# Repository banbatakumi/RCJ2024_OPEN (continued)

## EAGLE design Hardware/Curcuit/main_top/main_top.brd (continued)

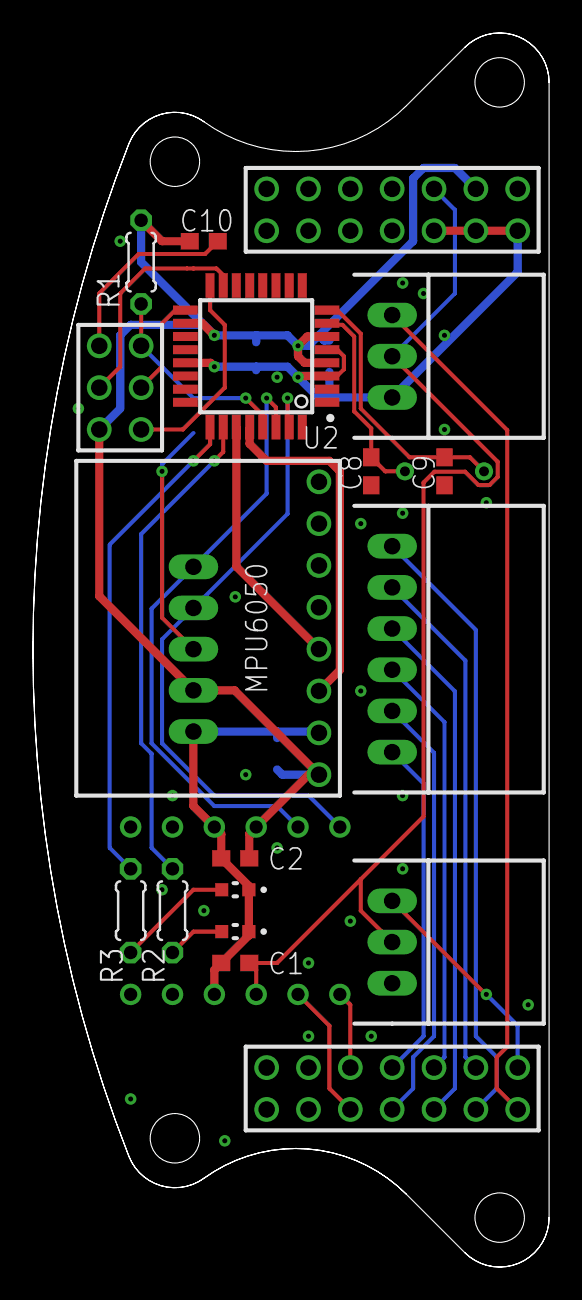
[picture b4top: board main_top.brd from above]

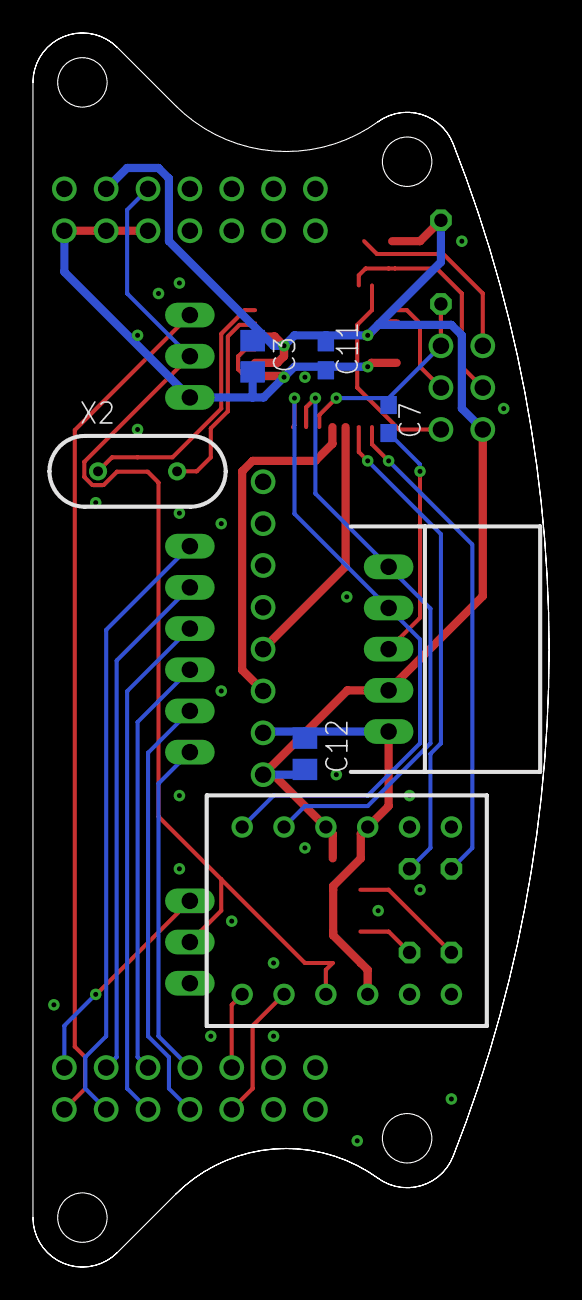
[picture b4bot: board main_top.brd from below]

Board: 2 copper layers, 31.3 x 74.9 mm, 25 parts (7 on the bottom side), 28 nets.

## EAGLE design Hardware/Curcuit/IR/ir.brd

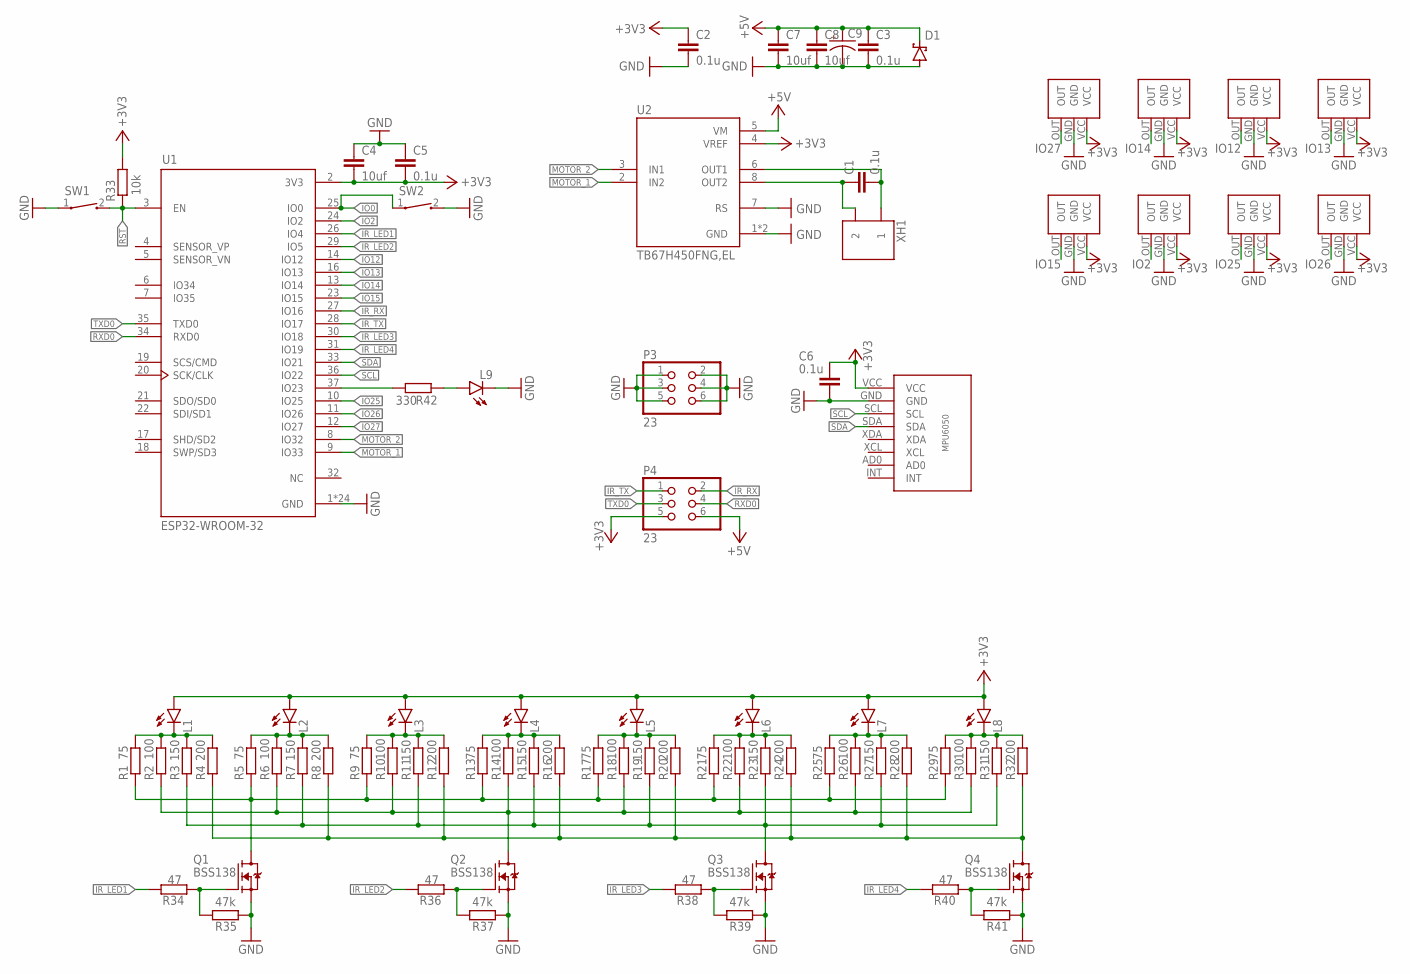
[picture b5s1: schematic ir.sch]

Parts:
C1, C2, C3, C5, C6: 0.1u; C0603
C4, C7, C8: 10uf; C0805
C9: MH5
D1: SS2040FL; SOD123FL
IR1, IR2, IR3, IR4, IR5, IR6, IR7, IR8: TSSP4038
L1, L2, L3, L4, L5, L6, L7, L8: LED
L9: SML-E12P8WT86; LED_SML-LXFM0603SIC-TR
P3, P4: 23; 2*3
Q1, Q2, Q3, Q4: BSS138; SOT95P240X111-3N
R1, R5, R9, R13, R17, R21, R25, R29: 75; R0603
R2, R6, R10, R14, R18, R22, R26, R30: 100; R0603
R3, R7, R11, R15, R19, R23, R27, R31: 150; R0603
R4, R8, R12, R16, R20, R24, R28, R32: 200; R0603
R33: 10k; R0603
R34, R36, R38, R40: 47; R0603
R35, R37, R39, R41: 47k; R0603
R42: 330; R0603
SW1, SW2: TATE
U1: ESP32-WROOM-32; MODULE_ESP32-WROOM-32
U2: TB67H450FNG,EL; SOIC127P599X175-9N
U$1: MPU6050
XH1: S2B

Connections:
+3V3: C2.1, C4.2, C5.2, C6.1, IR1.VCC, IR2.VCC, IR3.VCC, IR4.VCC, IR5.VCC, IR6.VCC, IR7.VCC, IR8.VCC, L1.+, L2.+, L3.+, L4.+, L5.+, L6.+, L7.+, L8.+, P4.5, R33.2, U1.2 (3V3), U2.4 (VREF), U$1.VCC
+5V: C3.1, C7.1, C8.1, C9.+, D1.C, P4.6, U2.5 (VM)
GND: C2.2, C3.2, C4.1, C5.1, C6.2, C7.2, C8.2, C9.-, D1.A, IR1.GND, IR2.GND, IR3.GND, IR4.GND, IR5.GND, IR6.GND, IR7.GND, IR8.GND, L9.C, P3.1, P3.2, P3.3, P3.4, P3.5, P3.6, Q1.2 (S), Q2.2 (S), Q3.2 (S), Q4.2 (S), R35.2, R37.2, R39.2, R41.2, SW1.1, SW2.2, U1.1 (GND), U1.15 (GND), U1.38 (GND), U1.39_1 (GND), U1.39_2 (GND), U1.39_3 (GND), U1.39_4 (GND), U1.39_5 (GND), U1.39_6 (GND), U1.39_7 (GND), U1.39_8 (GND), U1.39_9 (GND), U1.39_10 (GND), U1.39_11 (GND), U1.39_12 (GND), U1.39_13 (GND), U1.39_14 (GND), U1.39_15 (GND), U1.39_16 (GND), U1.39_17 (GND), U1.39_18 (GND), U1.39_19 (GND), U1.39_20 (GND), U1.39_21 (GND), U2.1 (GND), U2.7 (RS), U2.9 (GND), U$1.GND
IO0: SW2.1, U1.25 (IO0)
IO2: IR6.OUT, U1.24 (IO2)
IO12: IR3.OUT, U1.14 (IO12)
IO13: IR4.OUT, U1.16 (IO13)
IO14: IR2.OUT, U1.13 (IO14)
IO15: IR5.OUT, U1.23 (IO15)
IO25: IR7.OUT, U1.10 (IO25)
IO26: IR8.OUT, U1.11 (IO26)
IO27: IR1.OUT, U1.12 (IO27)
IR_LED1: R34.2, U1.26 (IO4)
IR_LED2: R36.2, U1.29 (IO5)
IR_LED3: R38.2, U1.30 (IO18)
IR_LED4: R40.2, U1.31 (IO19)
IR_RX: P4.2, U1.27 (IO16)
IR_TX: P4.1, U1.28 (IO17)
MOTOR_1: U1.9 (IO33), U2.2 (IN2)
MOTOR_2: U1.8 (IO32), U2.3 (IN1)
unnamed: C1.2, U2.6 (OUT1), XH1.1
unnamed: C1.1, U2.8 (OUT2), XH1.2
unnamed: L1.-, R1.2, R2.2, R3.2, R4.2
unnamed: L2.-, R5.2, R6.2, R7.2, R8.2
unnamed: L3.-, R9.2, R10.2, R11.2, R12.2
unnamed: L4.-, R13.2, R14.2, R15.2, R16.2
unnamed: L5.-, R17.2, R18.2, R19.2, R20.2
unnamed: L6.-, R21.2, R22.2, R23.2, R24.2
unnamed: L7.-, R25.2, R26.2, R27.2, R28.2
unnamed: L8.-, R29.2, R30.2, R31.2, R32.2
unnamed: Q1.3 (D), R1.1, R5.1, R9.1, R13.1, R17.1, R21.1, R25.1, R29.1
unnamed: Q2.3 (D), R2.1, R6.1, R10.1, R14.1, R18.1, R22.1, R26.1, R30.1
unnamed: Q3.3 (D), R3.1, R7.1, R11.1, R15.1, R19.1, R23.1, R27.1, R31.1
unnamed: Q4.3 (D), R4.1, R8.1, R12.1, R16.1, R20.1, R24.1, R28.1, R32.1
unnamed: Q1.1 (G), R34.1, R35.1
unnamed: Q2.1 (G), R36.1, R37.1
unnamed: Q3.1 (G), R38.1, R39.1
unnamed: Q4.1 (G), R40.1, R41.1
unnamed: L9.A, R42.1
unnamed: R42.2, U1.37 (IO23)
RST: R33.1, SW1.2, U1.3 (EN)
RXD0: P4.4, U1.34 (RXD0)
SCL: U1.36 (IO22), U$1.SCL
SDA: U1.33 (IO21), U$1.SDA
TXD0: P4.3, U1.35 (TXD0)

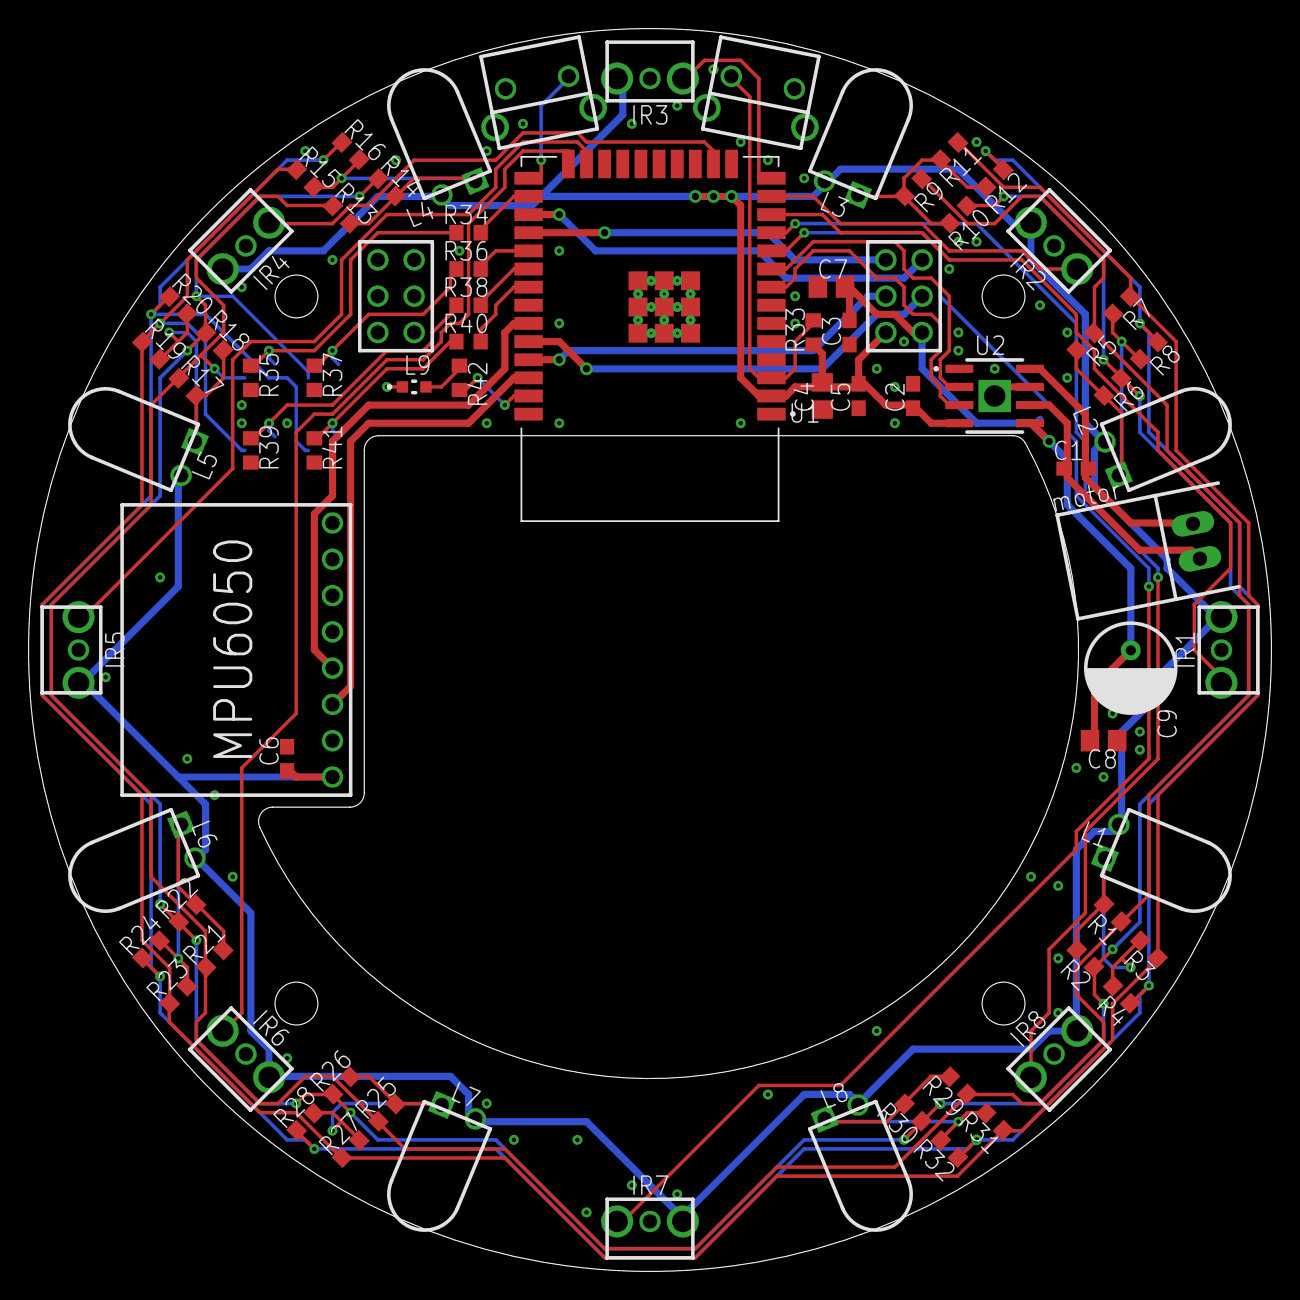
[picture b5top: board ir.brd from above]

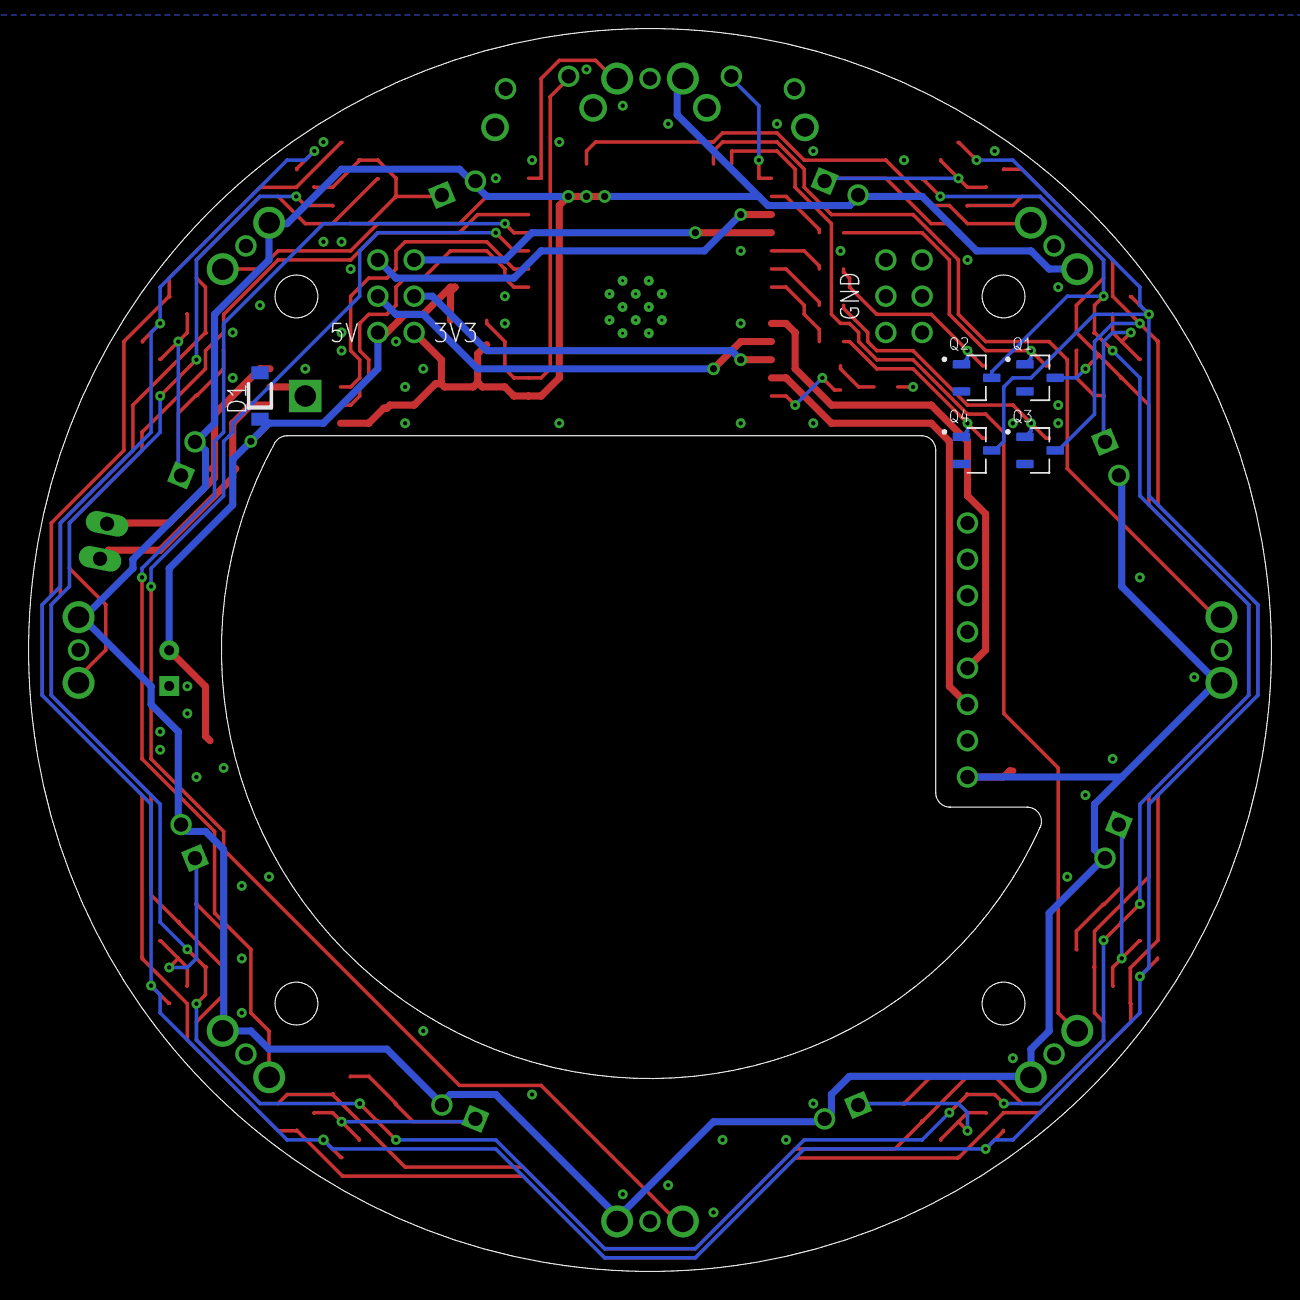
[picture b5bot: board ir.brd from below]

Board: 2 copper layers, 87.0 x 87.0 mm, 81 parts (5 on the bottom side), 45 nets.

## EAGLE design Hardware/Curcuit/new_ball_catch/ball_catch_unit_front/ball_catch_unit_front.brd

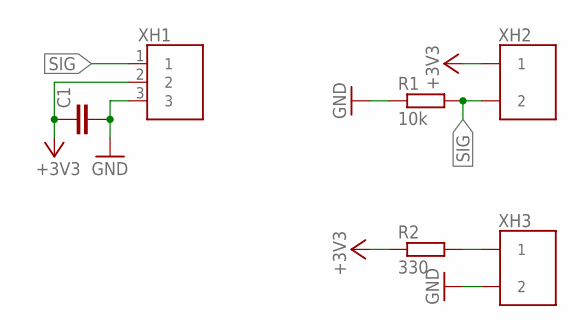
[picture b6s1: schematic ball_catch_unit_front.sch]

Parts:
C1: C-EUC0603; C0603
R1: 10k; 0204/7
R2: 330; 0204/7
XH1: S3B
XH2: 2B
XH3: S2B

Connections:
+3V3: C1.1, R2.1, XH1.2, XH2.1
GND: C1.2, R1.1, XH1.3, XH3.2
unnamed: R2.2, XH3.1
SIG: R1.2, XH1.1, XH2.2

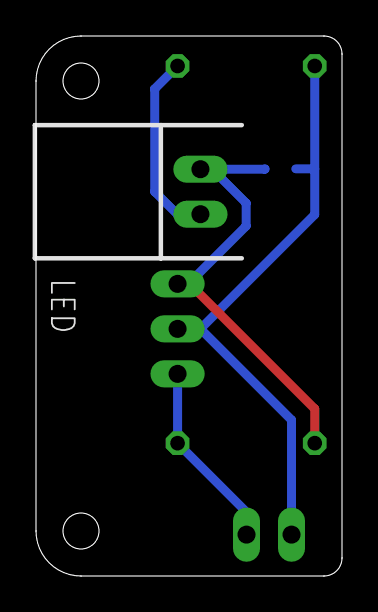
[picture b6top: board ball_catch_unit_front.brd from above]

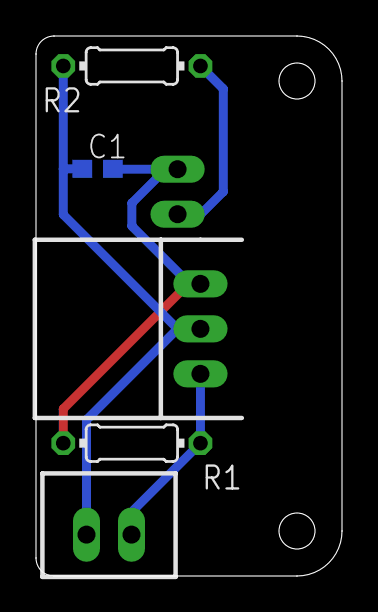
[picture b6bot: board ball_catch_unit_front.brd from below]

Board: 2 copper layers, 17.0 x 30.0 mm, 6 parts (5 on the bottom side), 4 nets.

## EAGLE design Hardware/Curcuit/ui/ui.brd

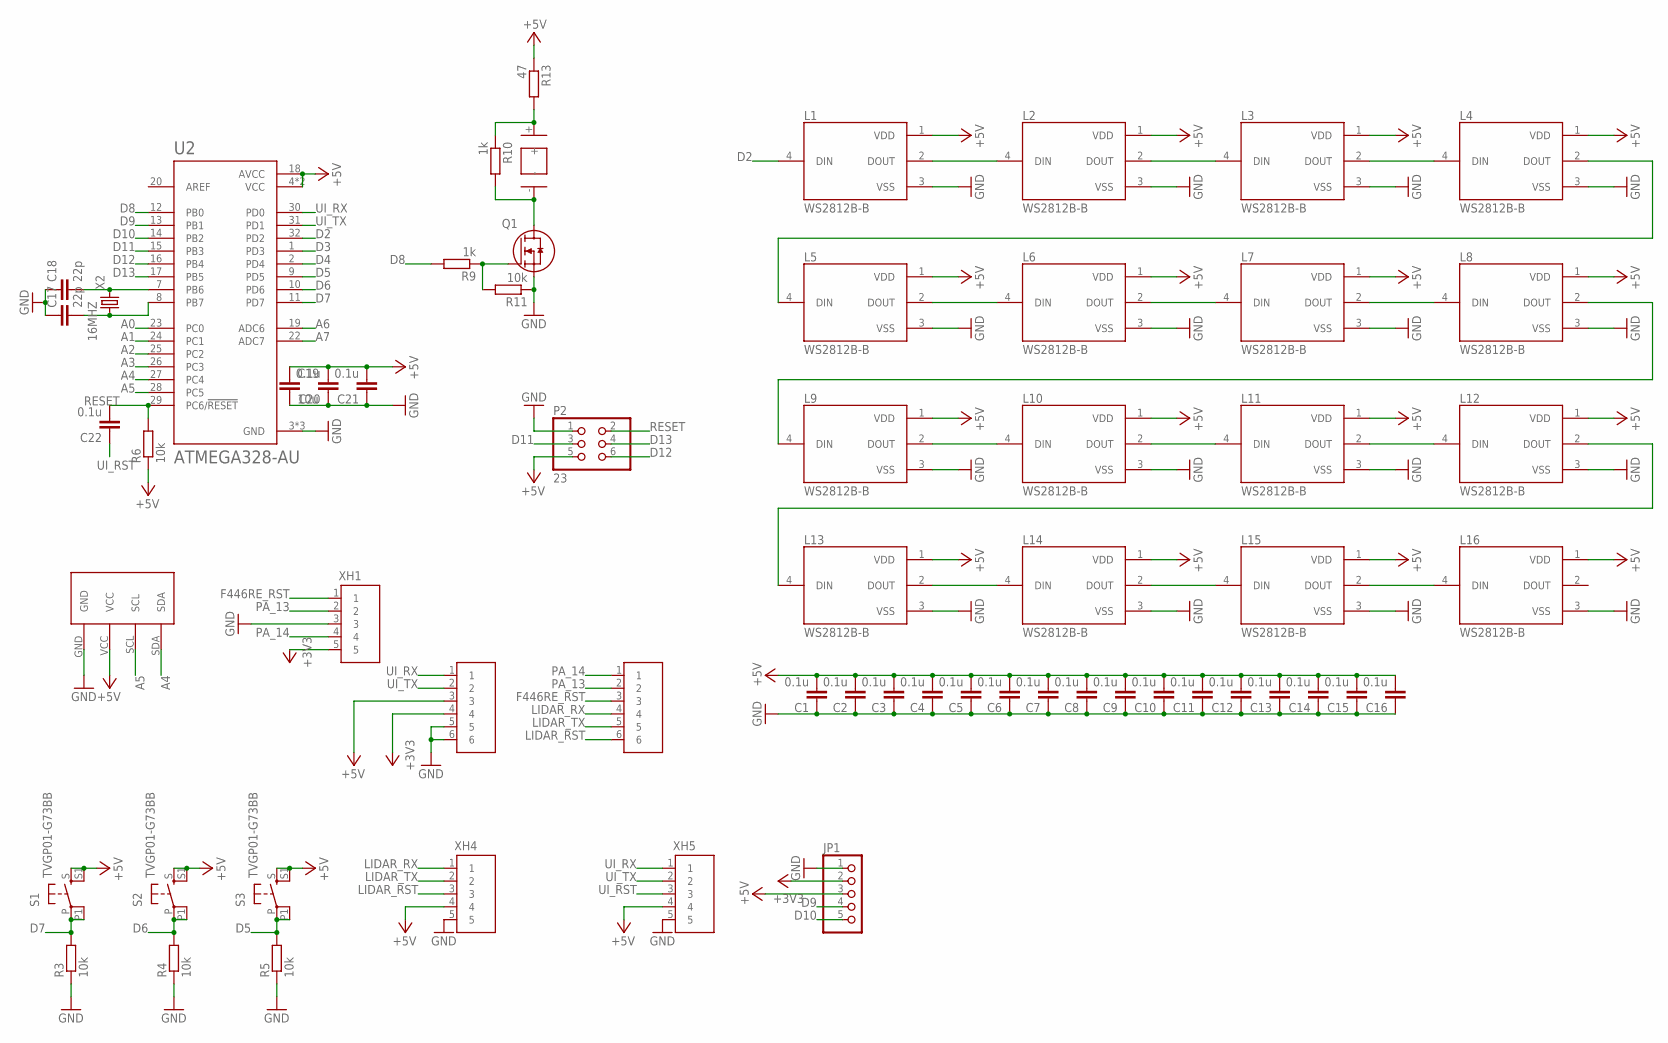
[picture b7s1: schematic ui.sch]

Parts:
B1: PKLCS1212E4001-R1
C1, C2, C3, C4, C5, C6, C7, C8, C9, C10, C11, C12, C13, C14, C15, C16, C20, C21, C22: 0.1u; C0603
C17, C18: 22p; C0603
C19: 10u; C0805
JP1: PINHD-1X5; 1X05
L1, L2, L3, L4, L5, L6, L7, L8, L9, L10, L11, L12, L13, L14, L15, L16: WS2812B-B; LED_WS2812B-B
P2: 23; 2*3
Q1: NP52N06SLG; TO230P1040X230-3N
R3, R4, R5, R6, R11: 10k; 0204/5
R9, R10: 1k; 0204/5
R13: 47; 0204/5
S1, S2, S3: TVGP01-G73BB
U1: SSD1306
U2: ATMEGA328-AU; QFP80P900X900X120-32N
X2: 16MHZ
XH1, XH4, XH5: S5B
XH2, XH3: S6B

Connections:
+3V3: JP1.2, XH1.5, XH2.4
+5V: C1.2, C2.2, C3.2, C4.2, C5.2, C6.2, C7.2, C8.2, C9.2, C10.2, C11.2, C12.2, C13.2, C14.2, C15.2, C16.2, C19.1, C20.2, C21.2, JP1.3, L1.1 (VDD), L2.1 (VDD), L3.1 (VDD), L4.1 (VDD), L5.1 (VDD), L6.1 (VDD), L7.1 (VDD), L8.1 (VDD), L9.1 (VDD), L10.1 (VDD), L11.1 (VDD), L12.1 (VDD), L13.1 (VDD), L14.1 (VDD), L15.1 (VDD), L16.1 (VDD), P2.5, R6.1, R13.1, S1.S, S1.S1, S2.S, S2.S1, S3.S, S3.S1, U1.VCC, U2.4 (VCC), U2.6 (VCC), U2.18 (AVCC), XH2.3, XH4.4, XH5.4
A0: U2.23 (PC0)
A1: U2.24 (PC1)
A2: U2.25 (PC2)
A3: U2.26 (PC3)
A4: U1.SDA, U2.27 (PC4)
A5: U1.SCL, U2.28 (PC5)
A6: U2.19 (ADC6)
A7: U2.22 (ADC7)
D2: L1.4 (DIN), U2.32 (PD2)
D3: U2.1 (PD3)
D4: U2.2 (PD4)
D5: R5.2, S3.P, S3.P1, U2.9 (PD5)
D6: R4.2, S2.P, S2.P1, U2.10 (PD6)
D7: R3.2, S1.P, S1.P1, U2.11 (PD7)
D8: R9.2, U2.12 (PB0)
D9: JP1.4, U2.13 (PB1)
D10: JP1.5, U2.14 (PB2)
D11: P2.3, U2.15 (PB3)
D12: P2.6, U2.16 (PB4)
D13: P2.4, U2.17 (PB5)
F446RE_RST: XH1.1, XH3.3
GND: C1.1, C2.1, C3.1, C4.1, C5.1, C6.1, C7.1, C8.1, C9.1, C10.1, C11.1, C12.1, C13.1, C14.1, C15.1, C16.1, C17.1, C18.1, C19.2, C20.1, C21.1, JP1.1, L1.3 (VSS), L2.3 (VSS), L3.3 (VSS), L4.3 (VSS), L5.3 (VSS), L6.3 (VSS), L7.3 (VSS), L8.3 (VSS), L9.3 (VSS), L10.3 (VSS), L11.3 (VSS), L12.3 (VSS), L13.3 (VSS), L14.3 (VSS), L15.3 (VSS), L16.3 (VSS), P2.1, Q1.S, R3.1, R4.1, R5.1, R11.1, U1.GND, U2.3 (GND), U2.5 (GND), U2.21 (GND), XH1.3, XH2.5, XH2.6, XH4.5, XH5.5
LIDAR_RST: XH3.6, XH4.3
LIDAR_RX: XH3.4, XH4.1
LIDAR_TX: XH3.5, XH4.2
unnamed: C18.2, U2.7 (PB6), X2.P$2 (2)
unnamed: C17.2, U2.8 (PB7), X2.P$1 (1)
unnamed: B1.-, Q1.D, R10.2
unnamed: L1.2 (DOUT), L2.4 (DIN)
unnamed: L2.2 (DOUT), L3.4 (DIN)
unnamed: L3.2 (DOUT), L4.4 (DIN)
unnamed: L4.2 (DOUT), L5.4 (DIN)
unnamed: L5.2 (DOUT), L6.4 (DIN)
unnamed: L6.2 (DOUT), L7.4 (DIN)
unnamed: L7.2 (DOUT), L8.4 (DIN)
unnamed: L8.2 (DOUT), L9.4 (DIN)
unnamed: Q1.G, R9.1, R11.2
unnamed: L9.2 (DOUT), L10.4 (DIN)
unnamed: L10.2 (DOUT), L11.4 (DIN)
unnamed: L11.2 (DOUT), L12.4 (DIN)
unnamed: L12.2 (DOUT), L13.4 (DIN)
unnamed: L13.2 (DOUT), L14.4 (DIN)
unnamed: L14.2 (DOUT), L15.4 (DIN)
unnamed: L15.2 (DOUT), L16.4 (DIN)
unnamed: B1.+, R10.1, R13.2
PA_13: XH1.2, XH3.2
PA_14: XH1.4, XH3.1
RESET: C22.2, P2.2, R6.2, U2.29 (PC6/!RESET)
UI_RST: C22.1, XH5.3
UI_RX: U2.30 (PD0), XH2.1, XH5.1
UI_TX: U2.31 (PD1), XH2.2, XH5.2

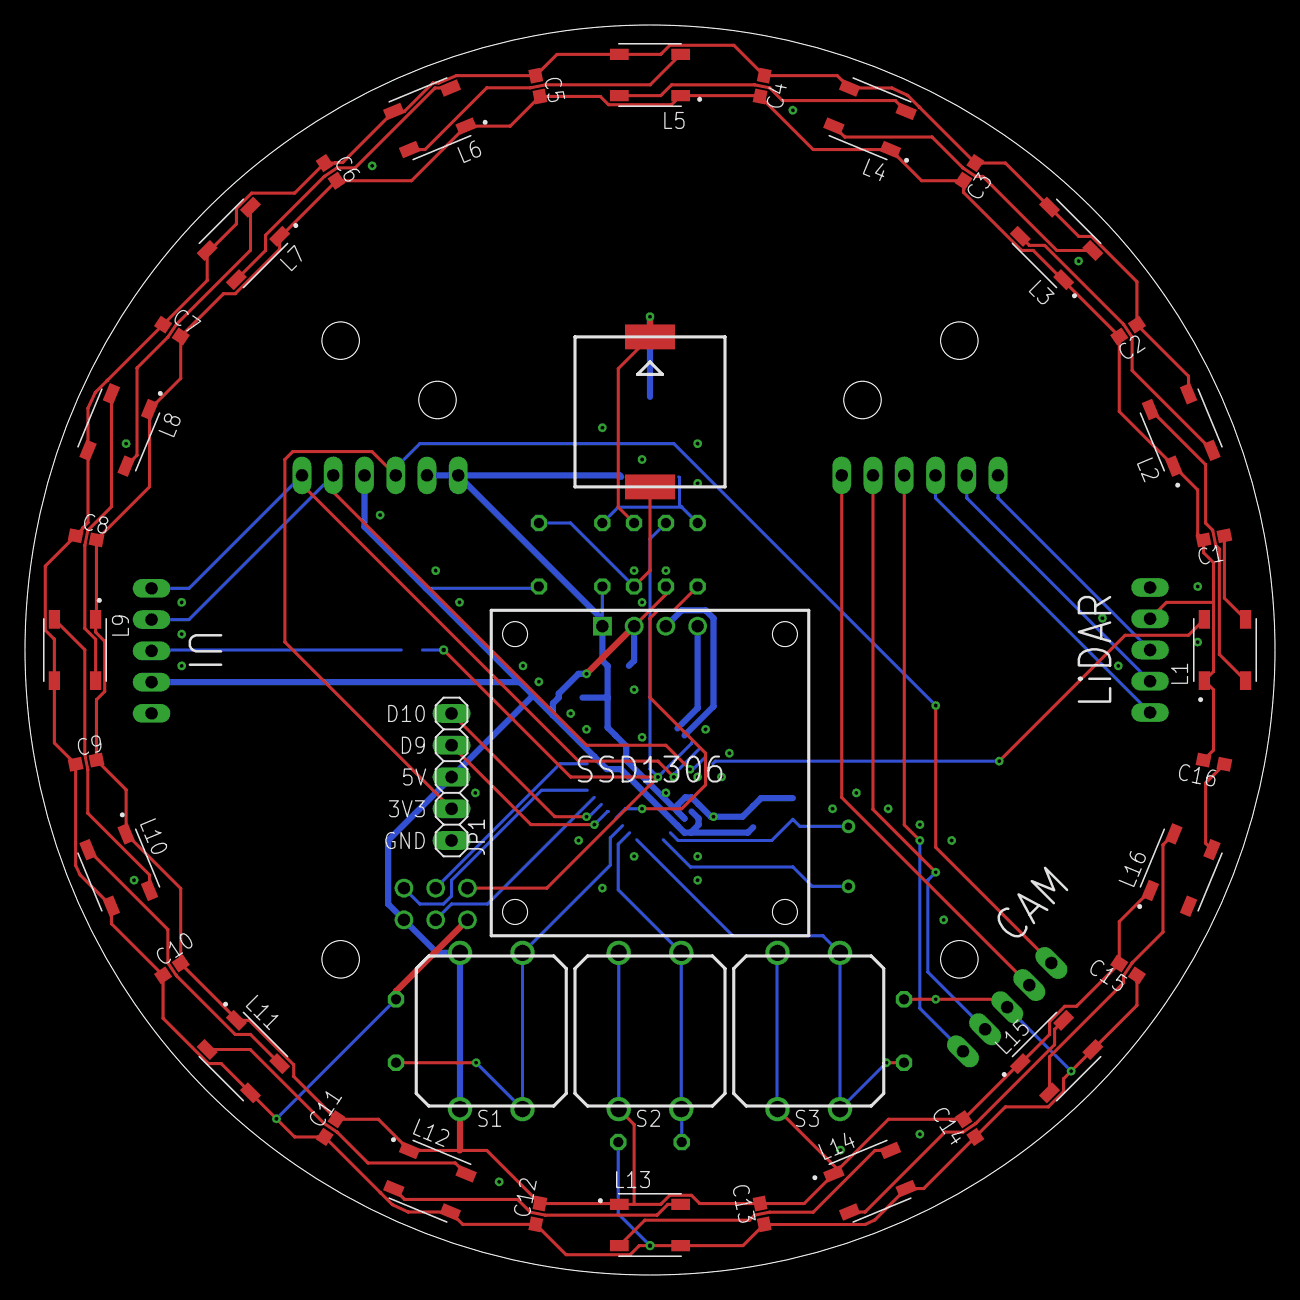
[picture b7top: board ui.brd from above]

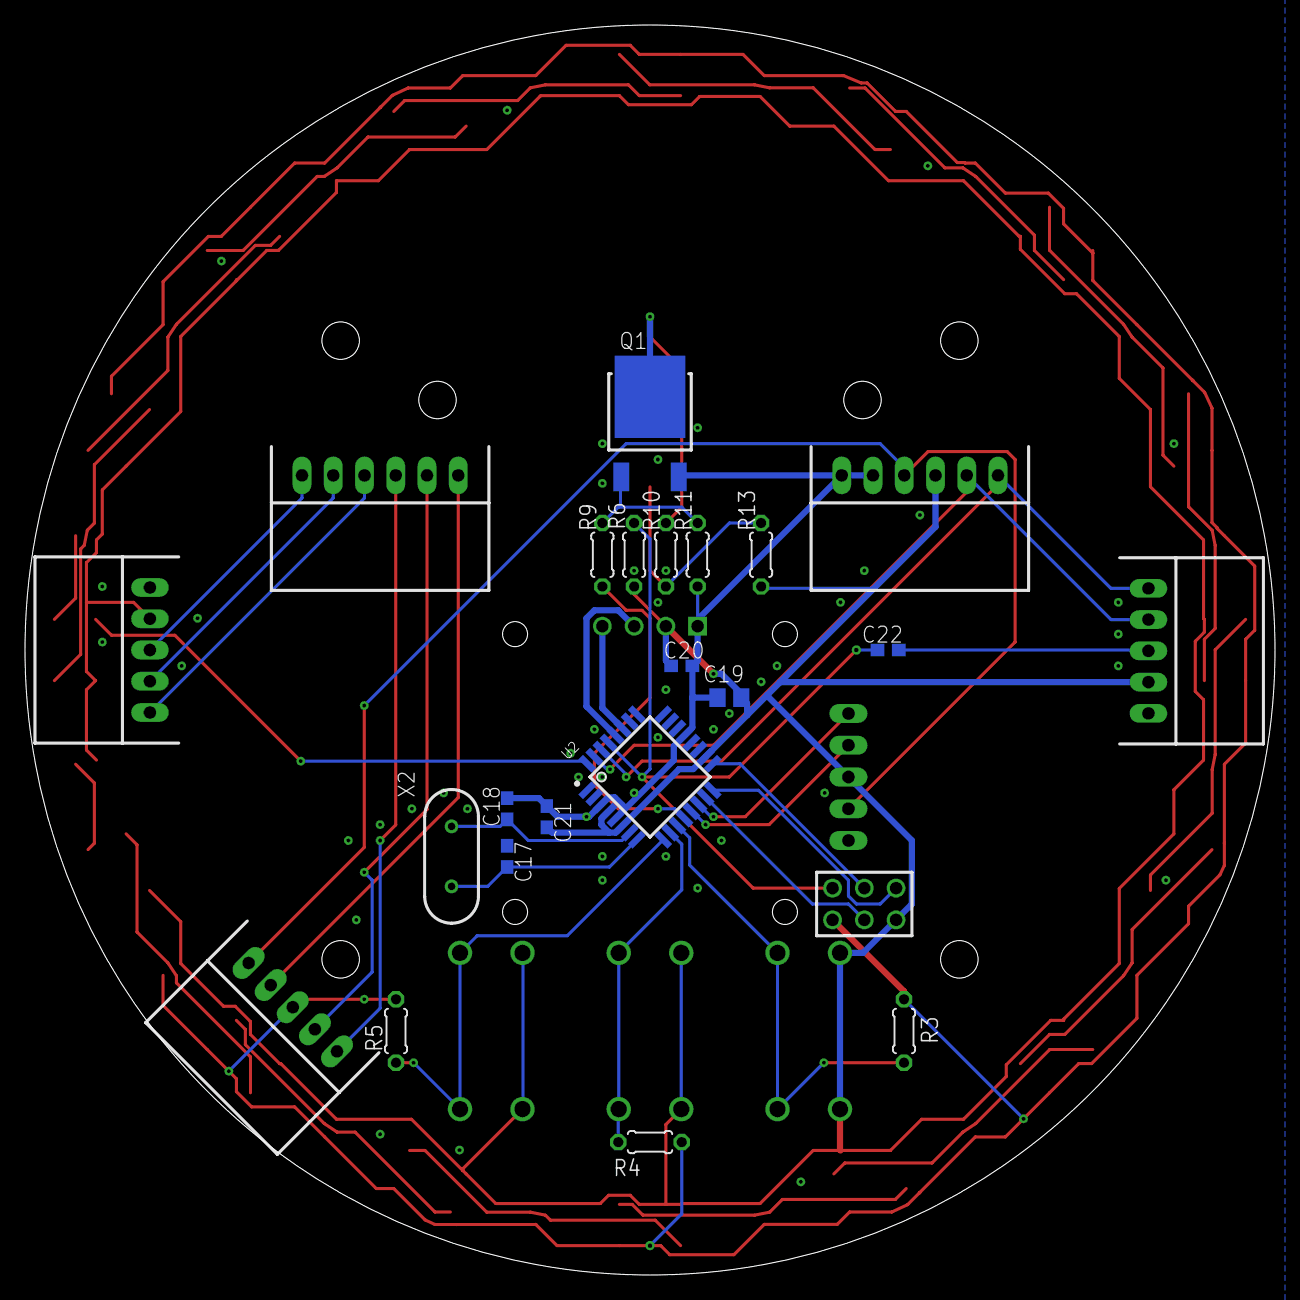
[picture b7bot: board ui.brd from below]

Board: 2 copper layers, 100.0 x 100.0 mm, 61 parts (23 on the bottom side), 45 nets.

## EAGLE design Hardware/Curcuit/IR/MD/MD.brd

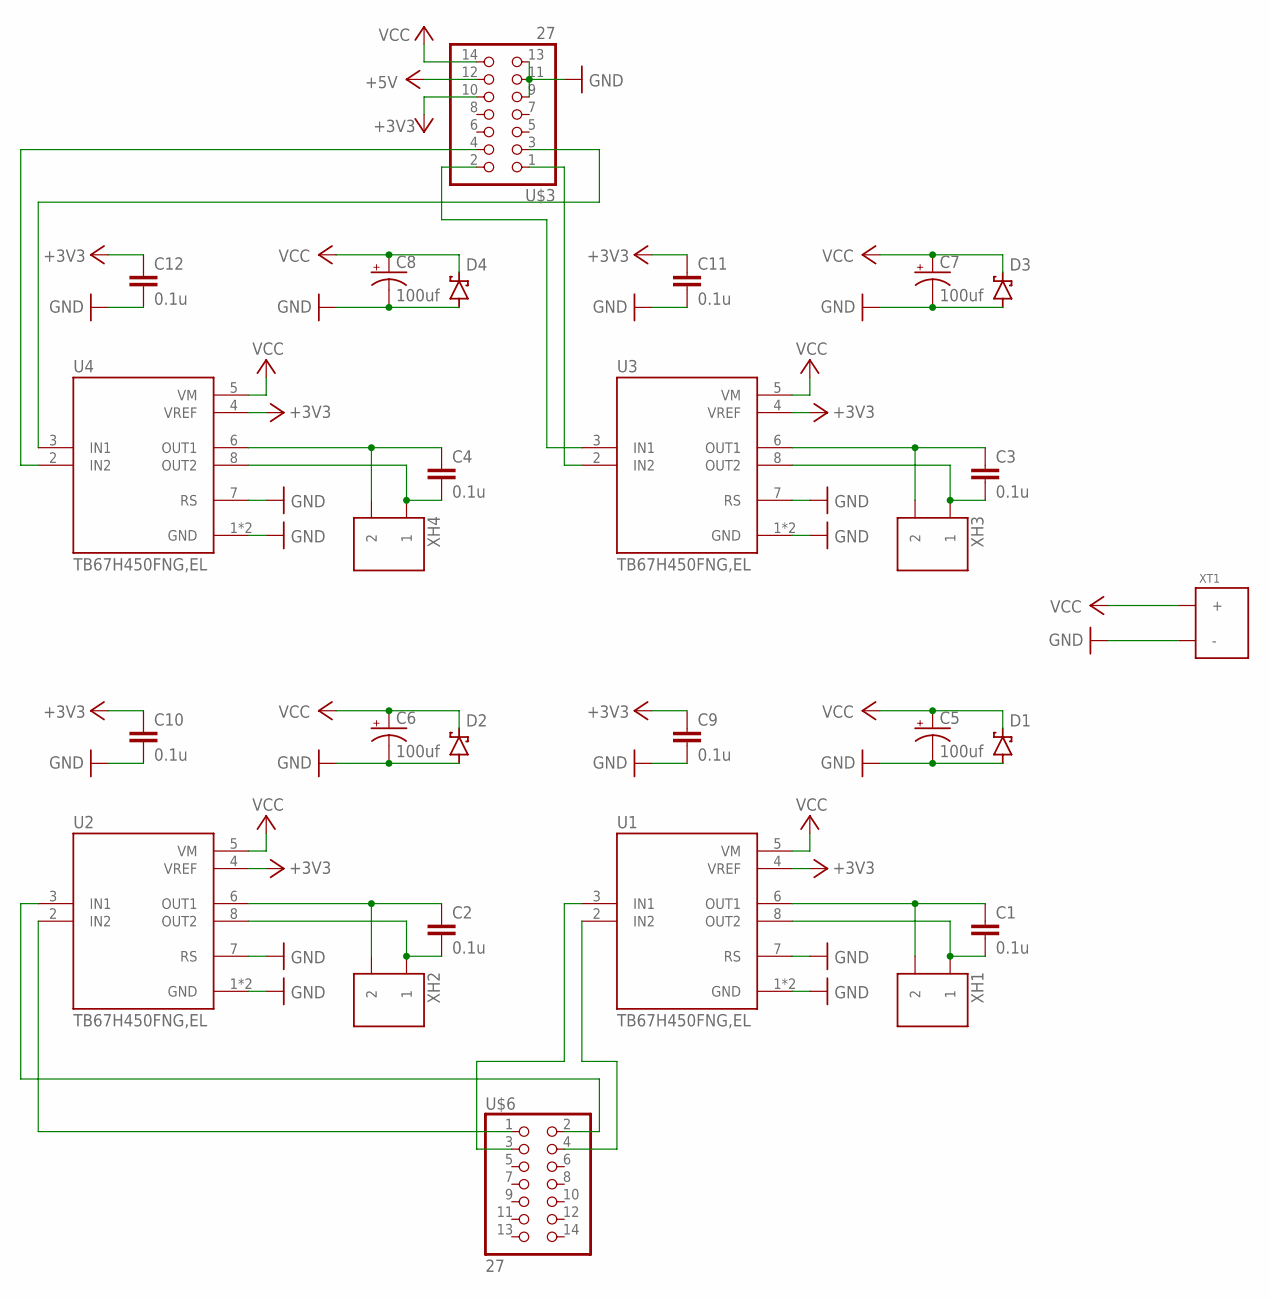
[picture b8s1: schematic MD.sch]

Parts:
C1, C2, C3, C4, C9, C10, C11, C12: 0.1u; C0603
C5, C6, C7, C8: 100uf; MH5
D1, D2, D3, D4: SS2040FL; SOD123FL
U1, U2, U3, U4: TB67H450FNG,EL; SOIC127P599X175-9N
U$3, U$6: 27; 2*7
XH1, XH2, XH3, XH4: S2B
XT1: XT30PW-M

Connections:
+3V3: C9.1, C10.1, C11.1, C12.1, U1.4 (VREF), U2.4 (VREF), U3.4 (VREF), U4.4 (VREF), U$3.10
+5V: U$3.12
GND: C5.-, C6.-, C7.-, C8.-, C9.2, C10.2, C11.2, C12.2, D1.A, D2.A, D3.A, D4.A, U1.1 (GND), U1.7 (RS), U1.9 (GND), U2.1 (GND), U2.7 (RS), U2.9 (GND), U3.1 (GND), U3.7 (RS), U3.9 (GND), U4.1 (GND), U4.7 (RS), U4.9 (GND), U$3.9, U$3.11, U$3.13, XT1.-
unnamed: U1.3 (IN1), U$6.3
unnamed: C1.1, U1.6 (OUT1), XH1.2
unnamed: C1.2, U1.8 (OUT2), XH1.1
unnamed: C2.1, U2.6 (OUT1), XH2.2
unnamed: U1.2 (IN2), U$6.4
unnamed: C2.2, U2.8 (OUT2), XH2.1
unnamed: C3.1, U3.6 (OUT1), XH3.2
unnamed: C3.2, U3.8 (OUT2), XH3.1
unnamed: C4.1, U4.6 (OUT1), XH4.2
unnamed: C4.2, U4.8 (OUT2), XH4.1
unnamed: U2.3 (IN1), U$6.2
unnamed: U2.2 (IN2), U$6.1
unnamed: U3.2 (IN2), U$3.1
unnamed: U3.3 (IN1), U$3.2
unnamed: U4.2 (IN2), U$3.4
unnamed: U4.3 (IN1), U$3.3
VCC: C5.+, C6.+, C7.+, C8.+, D1.C, D2.C, D3.C, D4.C, U1.5 (VM), U2.5 (VM), U3.5 (VM), U4.5 (VM), U$3.14, XT1.+

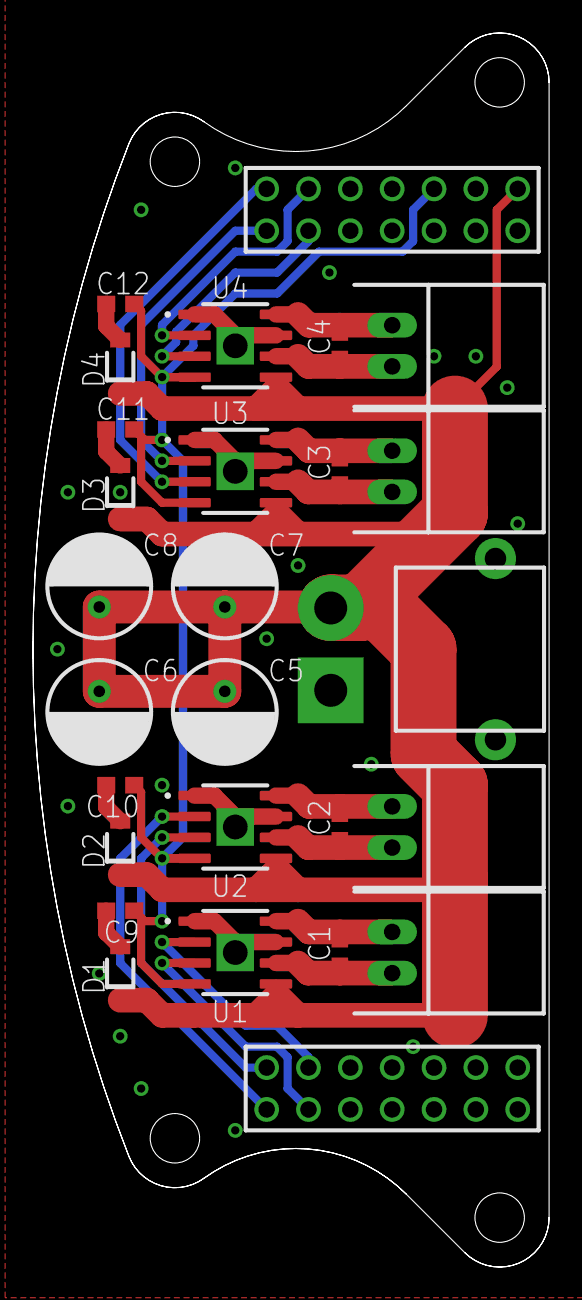
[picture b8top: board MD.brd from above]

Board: 2 copper layers, 31.3 x 74.9 mm, 27 parts (0 on the bottom side), 19 nets.

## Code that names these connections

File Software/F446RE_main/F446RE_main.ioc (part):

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Mcu.Name=STM32F446R(C-E)Tx
Mcu.Package=LQFP64
Mcu.UserName=STM32F446RETx
PA0-WKUP.Mode=Asynchronous
PA0-WKUP.Signal=UART4_TX
PA1.Mode=Asynchronous
PA1.Signal=UART4_RX
PA10.Mode=Asynchronous
PA10.Signal=USART1_RX
PA2.Mode=Asynchronous
PA2.Signal=USART2_TX
PA3.Mode=Asynchronous
PA3.Signal=USART2_RX
PA4.GPIOParameters=GPIO_Label
PA4.GPIO_Label=VOLTAGE
PA4.Signal=ADCx_IN4
PA5.GPIOParameters=GPIO_Label
PA5.GPIO_Label=LED1
PA5.Signal=GPIO_Output
PA6.GPIOParameters=GPIO_Label
PA6.GPIO_Label=LED_H
PA6.Signal=S_TIM13_CH1
PA9.Mode=Asynchronous
PA9.Signal=USART1_TX
PB10.GPIOParameters=GPIO_Label
PB10.GPIO_Label=MOTOR2A
PB10.Signal=S_TIM2_CH3
PB14.GPIOParameters=GPIO_Label
PB14.GPIO_Label=MOTOR1B
PB14.Signal=S_TIM12_CH1
PB15.GPIOParameters=GPIO_Label
PB15.GPIO_Label=MOTOR1A
PB15.Signal=S_TIM12_CH2
PB2.GPIOParameters=GPIO_Label
PB2.GPIO_Label=MOTOR2B
PB2.Signal=S_TIM2_CH4
PB3.GPIOParameters=GPIO_Label
PB3.GPIO_Label=MOTOR3B
PB3.Signal=S_TIM2_CH2
PB5.GPIOParameters=GPIO_Label
PB5.GPIO_Label=MOTOR3A
PB5.Signal=S_TIM3_CH2
PB6.GPIOParameters=GPIO_Label
PB6.GPIO_Label=FRONT_DRIBBLER_A
PB6.Signal=S_TIM4_CH1
PB7.GPIOParameters=GPIO_Label
PB7.GPIO_Label=FRONT_DRIBBLER_B
PB7.Signal=S_TIM4_CH2
PB8.GPIOParameters=GPIO_Label
PB8.GPIO_Label=BACK_DRIBBLER_A
PB8.Signal=S_TIM2_CH1_ETR
PB9.GPIOParameters=GPIO_Label
PB9.GPIO_Label=BACK_DRIBBLER_B
PB9.Signal=S_TIM4_CH4
PC0.GPIOParameters=GPIO_Label
PC0.GPIO_Label=KICKER_CHARGE
PC0.Signal=GPIO_Output
PC1.GPIOParameters=GPIO_Label
PC1.GPIO_Label=KICKER_KICK
PC1.Signal=GPIO_Output
PC10.Mode=Asynchronous
PC10.Signal=USART3_TX
PC11.Mode=Asynchronous
PC11.Signal=USART3_RX
PC12.Mode=Asynchronous
PC12.Signal=UART5_TX
PC4.GPIOParameters=GPIO_Label
PC4.GPIO_Label=HOLD_FRONT
PC4.Signal=ADCx_IN14
PC5.GPIOParameters=GPIO_Label
PC5.GPIO_Label=HOLD_BACK
PC5.Signal=ADCx_IN15
PC6.GPIOParameters=GPIO_Label
PC6.GPIO_Label=MOTOR4A
PC6.Signal=S_TIM3_CH1
PC8.GPIOParameters=GPIO_Label
PC8.GPIO_Label=MOTOR4B
PC8.Signal=S_TIM3_CH3
PD2.Mode=Asynchronous
PD2.Signal=UART5_RX
RCC.SYSCLKFreq_VALUE=180000000
RCC.SYSCLKSource=RCC_SYSCLKSOURCE_PLLCLK
board=custom

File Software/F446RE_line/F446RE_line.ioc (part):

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Mcu.Name=STM32F446R(C-E)Tx
Mcu.Package=LQFP64
Mcu.UserName=STM32F446RETx
PA2.GPIOParameters=GPIO_Label
PA2.GPIO_Label=MUX2X
PA2.Signal=ADCx_IN2
PA3.GPIOParameters=GPIO_Label
PA3.GPIO_Label=MUX2Y
PA3.Signal=ADCx_IN3
PA4.GPIOParameters=GPIO_Label
PA4.GPIO_Label=MUX2A
PA4.Signal=GPIO_Output
PA5.GPIOParameters=GPIO_Label
PA5.GPIO_Label=MUX2B
PA5.Signal=GPIO_Output
PA6.GPIOParameters=GPIO_Label
PA6.GPIO_Label=ENCODER4
PA6.Signal=ADCx_IN6
PA7.GPIOParameters=GPIO_Label
PA7.GPIO_Label=ENCODER2
PA7.Signal=ADCx_IN7
PB0.GPIOParameters=GPIO_Label
PB0.GPIO_Label=MUX3Y
PB0.Signal=ADCx_IN8
PB1.GPIOParameters=GPIO_Label
PB1.GPIO_Label=RIGHTSIDE_LINE
PB1.Signal=ADCx_IN9
PB12.GPIOParameters=GPIO_Label
PB12.GPIO_Label=MUX3A
PB12.Signal=GPIO_Output
PB13.GPIOParameters=GPIO_Label
PB13.GPIO_Label=MUX3B
PB13.Signal=GPIO_Output
PB7.GPIOParameters=GPIO_Label
PB7.GPIO_Label=MUX1A
PB7.Signal=GPIO_Output
PB9.GPIOParameters=GPIO_Label
PB9.GPIO_Label=MUX1B
PB9.Signal=GPIO_Output
PC0.GPIOParameters=GPIO_Label
PC0.GPIO_Label=MUX1X
PC0.Signal=ADCx_IN10
PC1.GPIOParameters=GPIO_Label
PC1.GPIO_Label=MUX1Y
PC1.Signal=ADCx_IN11
PC10.GPIOParameters=GPIO_Label
PC10.GPIO_Label=LED1
PC10.Signal=GPIO_Output
PC11.GPIOParameters=GPIO_Label
PC11.GPIO_Label=LED2
PC11.Signal=GPIO_Output
PC12.GPIOParameters=GPIO_Label
PC12.GPIO_Label=LED3
PC12.Signal=GPIO_Output
PC2.GPIOParameters=GPIO_Label
PC2.GPIO_Label=LEFTSIDE_LINE
PC2.Signal=ADCx_IN12
PC3.GPIOParameters=GPIO_Label
PC3.GPIO_Label=ENCODER3
PC3.Signal=ADCx_IN13
PC4.GPIOParameters=GPIO_Label
PC4.GPIO_Label=ENCODER1
PC4.Signal=ADCx_IN14
PC5.GPIOParameters=GPIO_Label
PC5.GPIO_Label=MUX3X
PC5.Signal=ADCx_IN15
PC6.Mode=Asynchronous
PC6.Signal=USART6_TX
PC7.Mode=Asynchronous
PC7.Signal=USART6_RX
PC8.GPIOParameters=GPIO_Label
PC8.GPIO_Label=LED_LINE
PC8.Signal=GPIO_Output
RCC.SYSCLKFreq_VALUE=180000000
RCC.SYSCLKSource=RCC_SYSCLKSOURCE_PLLCLK
board=custom

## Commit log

2025-04-19 add files
2025-04-20 add curcuit files
2025-04-20 閾値と待機時間変更
2025-04-20 cortex-debugの変数代入をコメントアウト
2025-04-20 cameraでゴールの大きさを可変にした
2025-04-20 デバッグモードの追加
2025-04-20 ちょっとだけ高速化
2025-04-20 ホモグラフィー行列生成プログラムの追加
2025-04-20 オーバークロックプログラム
2025-04-20 起動時安定化
2025-06-29 リツモリカップでの修正
2026-04-01 多分ライトモード追加
2026-04-01 リモコン対応
